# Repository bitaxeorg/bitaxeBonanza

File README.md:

bitaxeBonanza quad Intel BZM2 ASIC miner.

It is still an untested prototype! Don't build this expecting it to work out of the box. Do build it if you want to hack on some rad stuff.

- [Open Hardware License](LICENSE); Real Open Source.
	- [KiCAD](https://kicad.org) design files. 
- Four Intel BZM2 ASICs, powered in series.
	- Each BZM2 is [nominally](doc/specs.md) 0.7V with approx 350 GH/s @ 1.15 GHz hash frequency.
	- On chip digital temperature and voltage sensors
	- ntime rolling
- 11-13V XT30 input voltage
- TPS546D24S single-phase voltage regulator tuned for 2.8V output @ 20A
	- The voltage regulator backside power plane is exposed to hopefully thermally bond it with the main heatsink. 
- New fan control strategy (no more EMC2101)
- ESP32S3 for [esp-miner](https://github.com/bitaxeorg/esp-miner) support.
- 9-bit serial ASIC support via RP2040
    - Preliminary support with the [bitaxe-raw-pico](https://github.com/bitaxeorg/bitaxe-raw/tree/pico) firmware.
- Gerbers _not_ provided to discourage side hacks and AliEx slop. HMU if you need help generating gerbers with KiCad.

©️ [bitaxeorg](https://bitaxe.org)

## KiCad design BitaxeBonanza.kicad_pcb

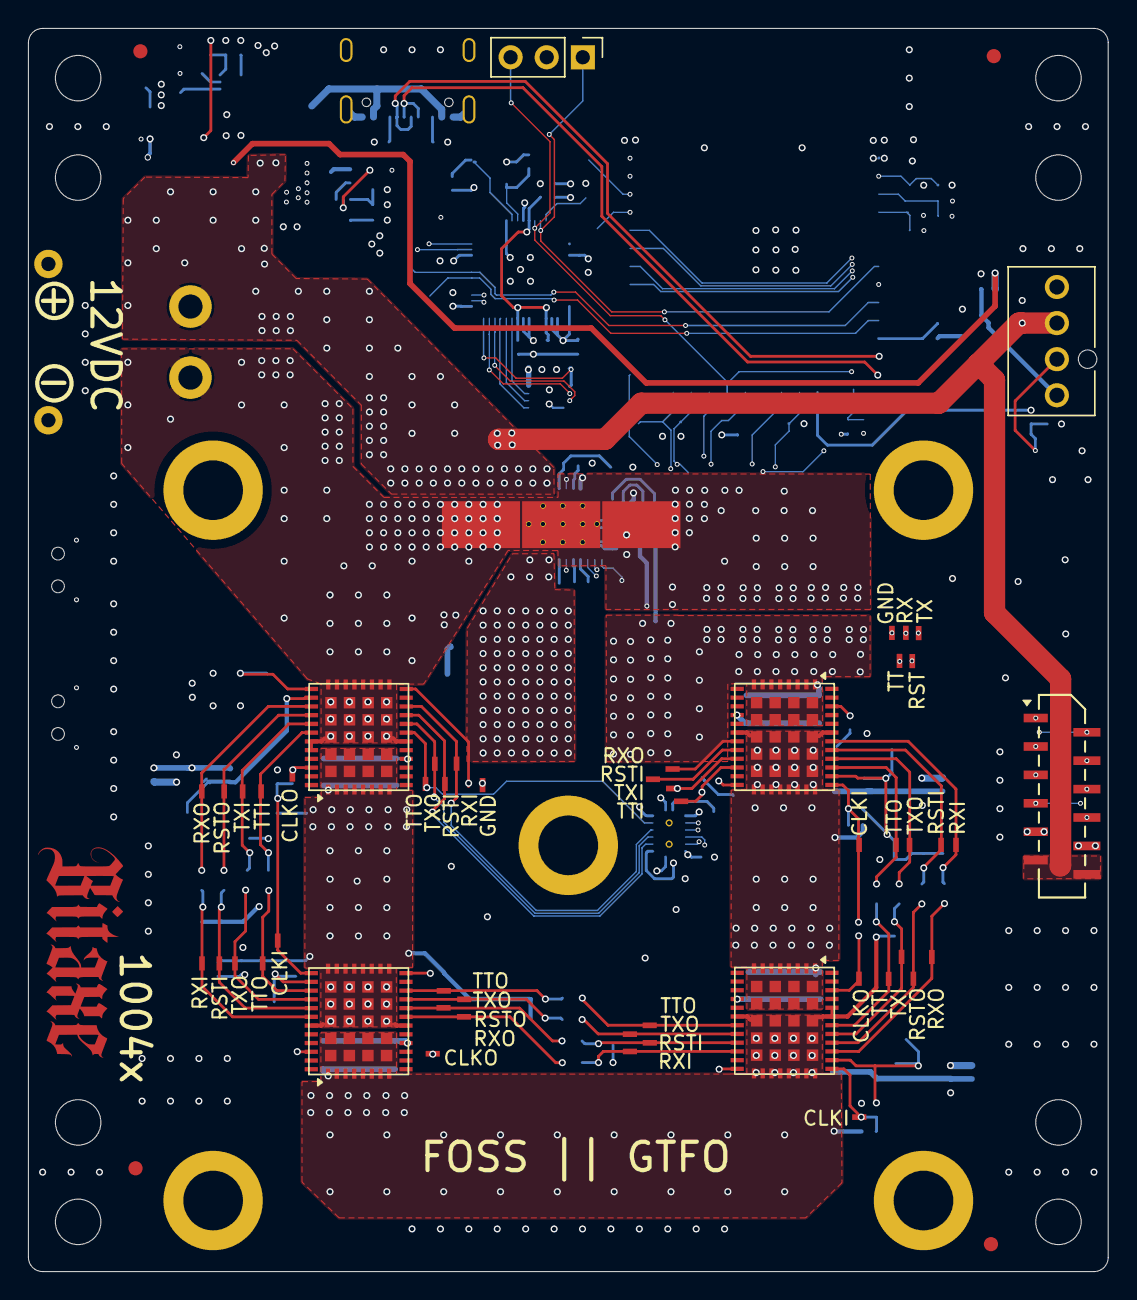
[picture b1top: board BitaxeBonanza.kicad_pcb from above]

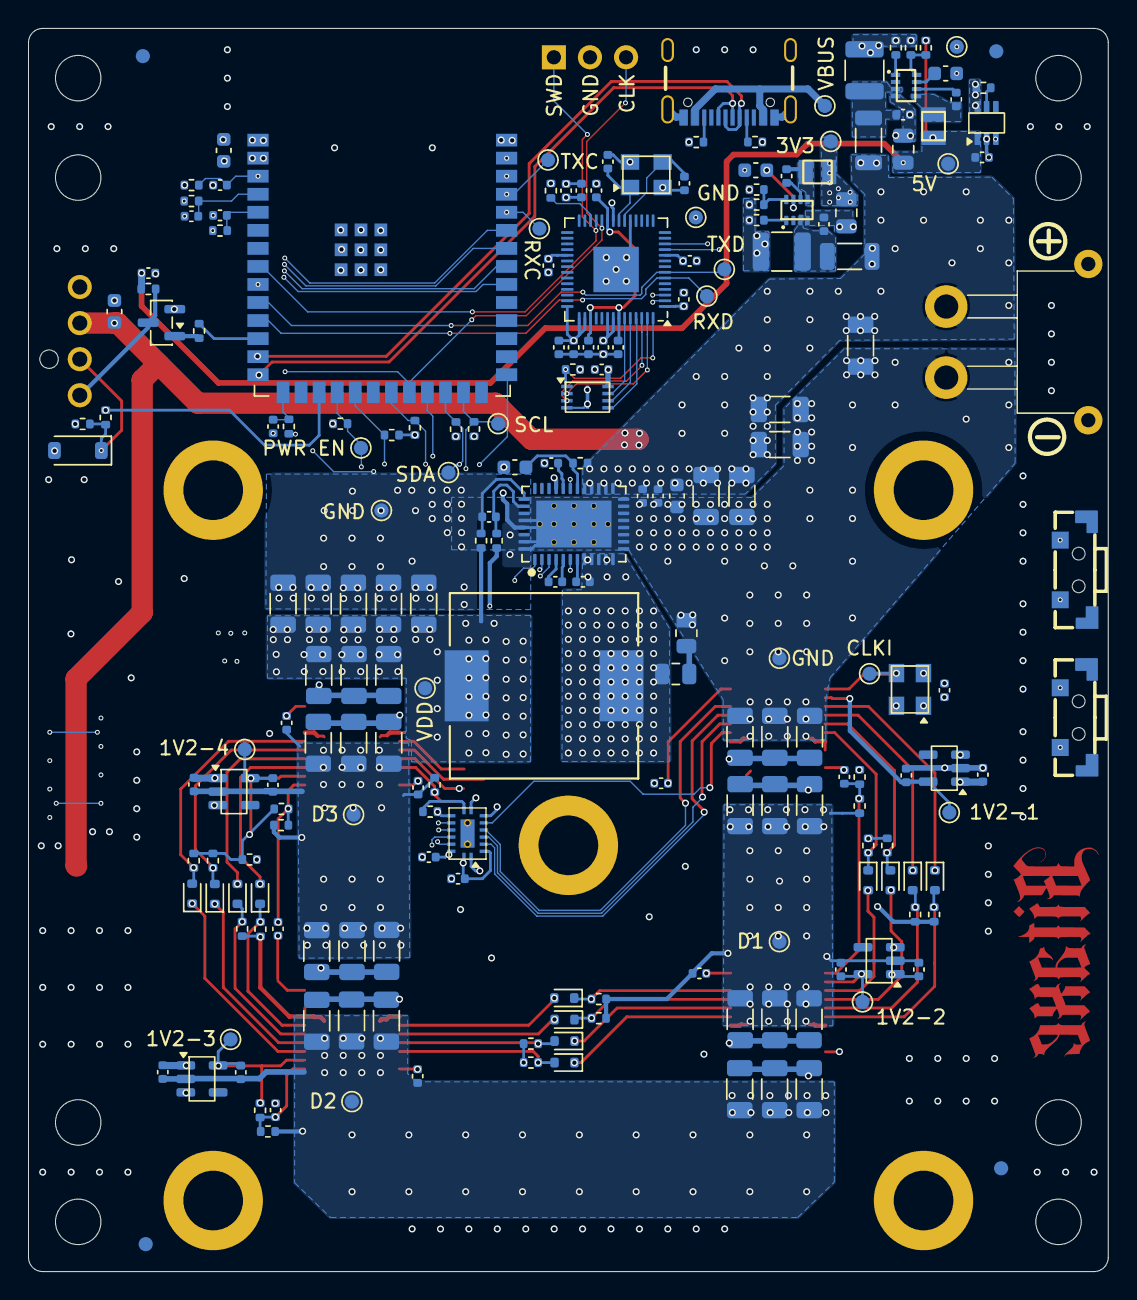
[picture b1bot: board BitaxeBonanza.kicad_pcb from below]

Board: 6 copper layers, 76.0 x 87.5 mm, 271 parts (210 on the bottom side), 135 nets.

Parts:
A1, A3: BZM2_MODE0; bzm2
A2, A4: BZM2_MODE1; bzm2
C2, C3, C4, C5, C6: 22uF; C_1206_3216Metric
C7, C15, C19, C25, C26, C27, C28, C34, C38, C39, C68, C72: 1uF; C_0402_1005Metric
C9, C10: 1uF; C_0603_1608Metric
C11: 4.7uF; C_0402_1005Metric
C13: 4.7nF; C_0402_1005Metric
C14: 2.2nF; C_0402_1005Metric
C16, C32, C36, C37, C40, C41, C42, C43, C44, C45, C46, C51, C52, C55, C56, C57, C58, C59, C67, C69, C70, C77: 0.1uF; C_0402_1005Metric
C17: 1000pF; C_0805_2012Metric
C18: 100pF; C_0402_1005Metric
C20: 47uF; C_1206_3216Metric
C21, C22, C23, C24, C83, C84, C85, C91, C92, C93, C99, C100, C101, C107, C108, C109, C115, C116, C117, C123, C124, C125, C131, C132, C133, C139, C140, C141: 100uF; C_1206_3216Metric
C33, C35: 30pF; C_0402_1005Metric
C47, C76: 10uF; C_0603_1608Metric
C48: 12pF; C_0402_1005Metric
C49, C50: 10uF; C_1210_3225Metric
C53, C54: 33nF; C_0603_1608Metric
C60, C61, C62, C63, C64: 120pF; C_0402_1005Metric
C65, C66: 22uF; C_0805_2012Metric
C142, C143, C144: 1000pF; C_0402_1005Metric
D1, D2, D3, D4, D5, D6, D7, D8, D9, D10, D11, D12: BAS516; D_SOD-523
D13: 3.3V Zener; D_SOD-123
FB1, FB2: FerriteBead; L_1206_3216Metric
FID1, FID2, FID3, FID4: Fiducial; Fiducial_1mm_Mask2mm
H1, H2, H3, H4, H5, H6, H7, H8: MountingHole_Pad; MountingHole_3.2mm_M3
HS1: Heatsink; Heatsink-5hole-BitaxeGT
J1: XT30; XT30PW-M
J2: Conn_01x03; PinHeader_1x03_P2.54mm_Vertical
J4: Conn_01x04; fan_connector
J5: Conn_01x12; CONN12_1-1735042-2
J6: TYPE-C-31-M-12; USB-C_SMD-TYPE-C-31-M-12_1
L1: 1.2uH; SRP1245A-180M_BRN
L2, L3: 1.5uH; IND-SMD_L2.0-W1.6
NT1: NetTie_2; NetTie-2_SMD_Pad0.2mmx1mm
Q1: BSS138; SOT-23
R1, R4, R17, R35, R36, R37, R38, R39, R40, R41, R42, R43, R44, R45, R46, R47, R48, R49, R50, R51, R52: 1k; R_0402_1005Metric
R2, R3, R9, R14, R22, R25, R34: 10k; R_0402_1005Metric
R5: 10; R_0402_1005Metric
R6: 1; R_0805_2012Metric
R7, R8: 49.9; R_0402_1005Metric
R15, R28: 15k; R_0402_1005Metric
R16: 49.9k; R_0402_1005Metric
R18, R19, R20, R21: 4.7k; R_0402_1005Metric
R23, R24, R30, R31, R32, R53: 5.1k; R_0402_1005Metric
R26: 20k; R_0402_1005Metric
R27: 47k; R_0402_1005Metric
R29: 27k; R_0402_1005Metric
R33: 5.6k; R_0402_1005Metric
SW3, SW4: SWITCH-SPST; SW-SMD_TC-S3601-3.5-260G-F0.6
TP1: PWR EN; TestPoint_Pad_D1.0mm
TP2: 1V2-2; TestPoint_Pad_D1.0mm
TP3: 1V2-3; TestPoint_Pad_D1.0mm
TP4: 1V2-4; TestPoint_Pad_D1.0mm
TP5: SDA; TestPoint_Pad_D1.0mm
TP6, TP13, TP32, TP51, TP55: RSTI; TestPoint_Pad_1.0x0.4mm
TP7: VDD; TestPoint_Pad_D1.0mm
TP8: SCL; TestPoint_Pad_D1.0mm
TP10: CLKI; TestPoint_Pad_D1.0mm
TP11, TP28, TP43: TTI; TestPoint_Pad_1.0x0.4mm
TP12, TP29, TP44: TXI; TestPoint_Pad_1.0x0.4mm
TP14, TP31, TP38, TP46: RXO; TestPoint_Pad_1.0x0.4mm
TP16: TXC; TestPoint_Pad_D1.0mm
TP17, TP33, TP40, TP50, TP54: TXO; TestPoint_Pad_1.0x0.4mm
TP18: 1V2-1; TestPoint_Pad_D1.0mm
TP19, TP26, TP27, TP61: GND; TestPoint_Pad_D1.0mm
TP20, TP36, TP52, TP56: RXI; TestPoint_Pad_1.0x0.4mm
TP21, TP34, TP41, TP49, TP53: TTO; TestPoint_Pad_1.0x0.4mm
TP22, TP69: GND; TestPoint_Pad_1.0x0.4mm
TP23: RXC; TestPoint_Pad_D1.0mm
TP24: TXD; TestPoint_Pad_D1.0mm
TP25: RXD; TestPoint_Pad_D1.0mm
TP30, TP39, TP45: RSTO; TestPoint_Pad_1.0x0.4mm
TP35, TP48, TP57: CLKI; TestPoint_Pad_1.0x0.4mm
TP37, TP42, TP47: CLKO; TestPoint_Pad_1.0x0.4mm
TP58: D1; TestPoint_Pad_D1.0mm
TP59: D2; TestPoint_Pad_D1.0mm
TP60: D3; TestPoint_Pad_D1.0mm
TP62: 3V3; TestPoint_Pad_D1.0mm
TP63: 5V; TestPoint_Pad_D1.0mm
TP64: VBUS; TestPoint_Pad_D1.0mm
TP65: TX; TestPoint_Pad_1.0x0.4mm
TP66: RX; TestPoint_Pad_1.0x0.4mm
TP67: TT; TestPoint_Pad_1.0x0.4mm
TP68: RST; TestPoint_Pad_1.0x0.4mm
U1, U3, U4, U6: MCP1824T-1202E/OT; SOT-23-5
U2: TPS546D24SRVFR; LQFN40-CLIP
U5: W25Q16JVUXIQ TR; USON-8_UX_2x3x0p6_WIN
U8: SN74AXC4T774; BQB0016A-MFG
U9: TPS22919DCKR; DCK0006A_N
U11: RP2040; RP2040-QFN-56-1EP_7x7mm_P0.4mm_EP3.2x3.2mm
U12: ESP32-S3-WROOM-1
U13, U14: TPS62933DRLR; SOT-583-8_L2.1-W1.2-P0.50-LS1.6-BR
U15, U16, U17: STHW4-DU-HN050206; PAD-SMD_L5.0-W2.0_STHW4-DU-HN050206
Y1: 12MHz; XTAL_ECS-120-20-33-CKM-TR3
Y2: 50MHz; OSC_ECS-3225MV-500-CN-TR

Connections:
/3V3: C32.2, C39.2, C40.2, C41.2, C42.2, C43.2, C44.2, C45.2, C46.2, C47.1, C59.1, C65.2, L2.2, R14.1, R16.2, R18.1, R19.2, R20.2, R21.2, R22.2, R27.2, R33.2, TP62.1 (1_1), U5.8 (VCC), U8.15 (VCCB), U11.1 (IOVDD), U11.10 (IOVDD), U11.22 (IOVDD), U11.33 (IOVDD), U11.42 (IOVDD), U11.43 (ADC_AVDD), U11.44 (VREG_IN), U11.48 (USB_VDD), U11.49 (IOVDD), U12.2 (3V3)
/5V: C34.1, C66.2, C77.1, L3.2, R29.2, R34.2, TP63.1 (1_1), U9.1 (IN)
/5V_SWITCH: C7.2, C25.2, C27.2, C68.2, R17.1, U1.1 (VIN), U1.3 (EN), U3.1 (VIN), U3.3 (EN), U4.1 (VIN), U4.3 (EN), U6.1 (VIN), U6.3 (EN), U9.6 (OUT)
/12V: C2.1, C3.1, C4.1, C5.1, C6.1, C9.1, C13.1, C14.1, C76.1, FB1.1, FB2.1, J1.1 (+V), J4.2, J5.11, J5.12, R5.1, U2.21 (PVIN), U2.22 (PVIN), U2.23 (PVIN), U2.24 (PVIN), U2.25 (PVIN)
/ASIC/1V2-1: A1.30 (VDDIO), C57.1, C58.1, C72.2, TP18.1 (1_1), U6.5 (VOUT), U8.2 (DIR2), U8.8 (DIR4), U8.16 (VCCA), Y2.1 (EN), Y2.4 (VIN)
/ASIC/1V2-2: A2.30 (VDDIO), C19.2, R37.2, R38.1, R39.1, TP2.1 (1_1), U1.5 (VOUT)
/ASIC/1V2-3: A3.30 (VDDIO), C26.2, R43.2, R44.1, R45.1, TP3.1 (1_1), U3.5 (VOUT)
/ASIC/1V2-4: A4.30 (VDDIO), C28.2, R4.1, R49.2, R50.1, R51.1, TP4.1 (1_1), U4.5 (VOUT)
/ASIC/GND2: A1.2 (VDD), A1.3 (VDD), A1.4 (VDD), A1.5 (VDD), A1.6 (VDD), A1.7 (VDD), A1.8 (VDD), A1.41 (VDD), A1.42 (VDD), A1.49 (VDD), A1.50 (VDD), A1.51 (VDD), A1.52 (VDD), A1.59 (VDD), A1.60 (VDD), A2.14 (VSS), A2.21 (VSS), A2.22 (VSS), A2.23 (VSS), A2.24 (VSS), A2.25 (VSS), A2.26 (VSS), A2.27 (VSS), A2.28 (VSS), A2.35 (VSS), A2.43 (VSS), A2.44 (VSS), A2.45 (VSS), A2.46 (VSS), A2.47 (VSS), A2.48 (VSS), A2.53 (VSS), A2.54 (VSS), A2.55 (VSS), A2.56 (VSS), A2.57 (VSS), A2.58 (VSS), C7.1, C19.1, C63.2, C83.2, C84.2, C85.2, C107.1, C108.1, C109.1, R40.2, R41.2, R42.2, R53.1, TP58.1 (1_1), U1.2 (GND)
/ASIC/GND3: A2.2 (VDD), A2.3 (VDD), A2.4 (VDD), A2.5 (VDD), A2.6 (VDD), A2.7 (VDD), A2.8 (VDD), A2.41 (VDD), A2.42 (VDD), A2.49 (VDD), A2.50 (VDD), A2.51 (VDD), A2.52 (VDD), A2.59 (VDD), A2.60 (VDD), A3.14 (VSS), A3.21 (VSS), A3.22 (VSS), A3.23 (VSS), A3.24 (VSS), A3.25 (VSS), A3.26 (VSS), A3.27 (VSS), A3.28 (VSS), A3.35 (VSS), A3.36 (PINSEL), A3.43 (VSS), A3.44 (VSS), A3.45 (VSS), A3.46 (VSS), A3.47 (VSS), A3.48 (VSS), A3.53 (VSS), A3.54 (VSS), A3.55 (VSS), A3.56 (VSS), A3.57 (VSS), A3.58 (VSS), C25.1, C26.1, C62.2, C99.2, C100.2, C101.2, C123.1, C124.1, C125.1, R32.1, R46.2, R47.2, R48.2, TP59.1 (1_1), U3.2 (GND)
/ASIC/GND4: A3.2 (VDD), A3.3 (VDD), A3.4 (VDD), A3.5 (VDD), A3.6 (VDD), A3.7 (VDD), A3.8 (VDD), A3.41 (VDD), A3.42 (VDD), A3.49 (VDD), A3.50 (VDD), A3.51 (VDD), A3.52 (VDD), A3.59 (VDD), A3.60 (VDD), A4.14 (VSS), A4.21 (VSS), A4.22 (VSS), A4.23 (VSS), A4.24 (VSS), A4.25 (VSS), A4.26 (VSS), A4.27 (VSS), A4.28 (VSS), A4.35 (VSS), A4.43 (VSS), A4.44 (VSS), A4.45 (VSS), A4.46 (VSS), A4.47 (VSS), A4.48 (VSS), A4.53 (VSS), A4.54 (VSS), A4.55 (VSS), A4.56 (VSS), A4.57 (VSS), A4.58 (VSS), C27.1, C28.1, C60.2, C61.2, C115.2, C116.2, C117.2, C139.1, C140.1, C141.1, R9.2, R31.1, R52.2, TP60.1 (1_1), U4.2 (GND)
/ASIC/REFCLKIN1: A1.29 (REFCLKIN), TP10.1 (1_1), Y2.3 (OUT)
/ASIC/REFCLKIN2: A2.29 (REFCLKIN), C142.2, R39.2, R40.1, TP35.1 (1_1)
/ASIC/REFCLKIN3: A3.29 (REFCLKIN), C143.2, R45.2, R46.1, TP57.1 (1_1)
/ASIC/REFCLKIN4: A4.29 (REFCLKIN), C144.2, R51.2, R52.1, TP48.1 (1_1)
/ASIC/REFCLKOUT1: A1.38 (REFCLKOUT1), C142.1, TP37.1 (1_1)
/ASIC/REFCLKOUT2: A2.38 (REFCLKOUT1), C143.1, TP42.1 (1_1)
/ASIC/REFCLKOUT3: A3.38 (REFCLKOUT1), C144.1, TP47.1 (1_1)
/ASIC/RST_1V2: A1.17 (RESET_IN), TP6.1 (1_1), U8.3 (A1)
/ASIC/RST_3V3: TP68.1 (1_1), U8.14 (B1), U12.39 (GPIO1/TOUCH1/ADC1_CH0)
/ASIC/RX_1V2: A1.18 (RX_IN), TP20.1 (1_1), U8.5 (A3)
/ASIC/RX_3V3: TP66.1 (1_1), U8.12 (B3), U11.11 (GPIO8)
/ASIC/TRIP_1V2: A1.15 (TRIP_OUT), TP21.1 (1_1), U8.6 (A4)
/ASIC/TRIP_3V3: TP67.1 (1_1), U8.11 (B4), U12.38 (GPIO2/TOUCH2/ADC1_CH1)
/ASIC/TX_1V2: A1.16 (TX_OUT), TP17.1 (1_1), U8.4 (A2)
/ASIC/TX_3V3: TP65.1 (1_1), U8.13 (B2), U11.12 (GPIO9)
/ASIC/bypass1-1/out: A1.1 (VDD_INT_1), C83.1, C84.1, C85.1
/ASIC/bypass1-2/in: A1.12 (VDD_INT_2), C91.2, C92.2, C93.2
/ASIC/bypass2-1/out: A2.1 (VDD_INT_1), C99.1, C100.1, C101.1
/ASIC/bypass2-2/in: A2.12 (VDD_INT_2), C107.2, C108.2, C109.2
/ASIC/bypass3-1/out: A3.1 (VDD_INT_1), C115.1, C116.1, C117.1
/ASIC/bypass3-2/in: A3.12 (VDD_INT_2), C123.2, C124.2, C125.2
/ASIC/bypass4-1/out: A4.1 (VDD_INT_1), C131.1, C132.1, C133.1
/ASIC/bypass4-2/in: A4.12 (VDD_INT_2), C139.2, C140.2, C141.2
/ASIC/shifter1-2/RESET_IN: A2.33 (RESET_IN), D3.A, R37.1, TP32.1 (1_1)
/ASIC/shifter1-2/RESET_OUT: A1.32 (RESET_OUT), D3.K, TP30.1 (1_1)
/ASIC/shifter1-2/RX_IN: A2.34 (RX_IN), D4.A, R38.2, TP36.1 (1_1)
/ASIC/shifter1-2/RX_OUT: A1.31 (RX_OUT), D4.K, TP31.1 (1_1)
/ASIC/shifter1-2/TRIP_IN: A1.34 (TRIP_IN), D1.K, R35.1, TP28.1 (1_1)
/ASIC/shifter1-2/TRIP_OUT: A2.31 (TRIP_OUT), D1.A, TP34.1 (1_1)
/ASIC/shifter1-2/TX_IN: A1.33 (TX_IN), D2.K, R36.1, TP29.1 (1_1)
/ASIC/shifter1-2/TX_OUT: A2.32 (TX_OUT), D2.A, TP33.1 (1_1)
/ASIC/shifter2-3/RESET_IN: A3.17 (RESET_IN), D7.A, R43.1, TP55.1 (1_1)
/ASIC/shifter2-3/RESET_OUT: A2.16 (RESET_OUT), D7.K, TP39.1 (1_1)
/ASIC/shifter2-3/RX_IN: A3.18 (RX_IN), D8.A, R44.2, TP56.1 (1_1)
/ASIC/shifter2-3/RX_OUT: A2.15 (RX_OUT), D8.K, TP38.1 (1_1)
/ASIC/shifter2-3/TRIP_IN: A2.18 (TRIP_IN), D5.K, R41.1, TP41.1 (1_1)
/ASIC/shifter2-3/TRIP_OUT: A3.15 (TRIP_OUT), D5.A, TP53.1 (1_1)
/ASIC/shifter2-3/TX_IN: A2.17 (TX_IN), D6.K, R42.1, TP40.1 (1_1)
/ASIC/shifter2-3/TX_OUT: A3.16 (TX_OUT), D6.A, TP54.1 (1_1)
/ASIC/shifter3-4/RESET_IN: A4.33 (RESET_IN), D11.A, R49.1, TP51.1 (1_1)
/ASIC/shifter3-4/RESET_OUT: A3.32 (RESET_OUT), D11.K, TP45.1 (1_1)
/ASIC/shifter3-4/RX_IN: A4.34 (RX_IN), D12.A, R50.2, TP52.1 (1_1)
/ASIC/shifter3-4/RX_OUT: A3.31 (RX_OUT), D12.K, TP46.1 (1_1)
/ASIC/shifter3-4/TRIP_IN: A3.34 (TRIP_IN), D9.K, R47.1, TP43.1 (1_1)
/ASIC/shifter3-4/TRIP_OUT: A4.31 (TRIP_OUT), D9.A, TP49.1 (1_1)
/ASIC/shifter3-4/TX_IN: A3.33 (TX_IN), D10.K, R48.1, TP44.1 (1_1)
/ASIC/shifter3-4/TX_OUT: A4.32 (TX_OUT), D10.A, TP50.1 (1_1)
/Data/1V1: C36.2, C37.2, C38.2, U11.23 (DVDD), U11.45 (VREG_VOUT), U11.50 (DVDD)
/Data/5V_EN: U9.3 (ON), U12.23 (GPIO21)
/Data/DISP_GPIO1: J5.8, U12.35 (MTMS/GPIO42)
/Data/DISP_GPIO2: J5.7, U12.34 (MTDI/GPIO41/CLK_OUT1)
/Data/DISP_RX: J5.4, U12.33 (MTDO/GPIO40/CLK_OUT2)
/Data/DISP_TX: J5.5, U12.32 (MTCK/GPIO39/CLK_OUT3/SUBSPICS1)
/Data/EN: C48.1, R22.1, SW3.2, U12.3 (EN)
/Data/ESP32_RX_CTRL: TP23.1 (1_1), U11.2 (GPIO0), U12.36 (U0RXD/GPIO44/CLK_OUT2)
/Data/ESP32_RX_DATA: TP25.1 (1_1), U11.6 (GPIO4), U12.11 (GPIO18/U1RXD/ADC2_CH7/CLK_OUT3)
/Data/ESP32_TX_CTRL: TP16.1 (1_1), U11.3 (GPIO1), U12.37 (U0TXD/GPIO43/CLK_OUT1)
/Data/ESP32_TX_DATA: TP24.1 (1_1), U11.7 (GPIO5), U12.10 (GPIO17/U1TXD/ADC2_CH6)
/Data/FAN_PWM: R1.2, U12.12 (GPIO8/TOUCH8/ADC1_CH7/SUBSPICS1)
/Data/FAN_TACH: R2.2, U12.17 (GPIO9/TOUCH9/ADC1_CH8/FSPIHD/SUBSPIHD)
/Data/IO0: SW4.2, U12.27 (GPIO0/BOOT*)
/Data/PWR_EN: R3.2, TP1.1 (1_1), U2.27 (EN/UVLO), U12.18 (GPIO10/TOUCH10/ADC1_CH9/FSPICS0/FSPIIO4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)
/Data/QSPI_SCLK: U5.6 (CLK), U11.52 (QSPI_SCLK)
/Data/QSPI_SD0: U5.5 (DI(IO0)), U11.53 (QSPI_SD0)
/Data/QSPI_SD1: U5.2 (DO(IO1)), U11.55 (QSPI_SD1)
/Data/QSPI_SD2: U5.3 (/WP(IO2)), U11.54 (QSPI_SD2)
/Data/QSPI_SD3: U5.7 (/HOLDOR/RESET(IO3)), U11.51 (QSPI_SD3)
/Data/QSPI_SS: R14.2, U5.1 (/CS), U11.56 (QSPI_SS)
/Data/SCL: R19.1, TP8.1 (1_1), U2.3 (PMB_CLK), U12.25 (GPIO48/SPICLK_N/SUBSPICLK_N_DIFF)
/Data/SDA: R18.2, TP5.1 (1_1), U2.2 (PMB_DATA), U12.24 (GPIO47/SPICLK_P/SUBSPICLK_P_DIFF)
/Data/SMB_ALRT: R20.1, U2.6 (SMB_ALRT), U12.21 (GPIO13/TOUCH13/ADC2_CH2/FSPIQ/FSPIIO7/S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)
/Data/SWCLK: J2.3, J5.1, U11.24 (SWCLK), U12.22 (GPIO14/TOUCH14/ADC2_CH3/FSPIWP/FSPIDQS/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)
/Data/SWD-BRIDGE: J2.1, U11.25 (SWD), U12.8 (GPIO15/U0RTS/ADC2_CH4/XTAL_32K_P)
/Data/SWD-DISP: J5.2, U12.9 (GPIO16/U0CTS/ADC2_CH5/XTAL_32K_NH5)
/Data/USB_D+: J6.A6 (DP1), J6.B6 (DP2), U12.14 (GPIO20/U1CTS/ADC2_CH9/CLK_OUT1/USB_D+)
/Data/USB_D-: J6.A7 (DN1), J6.B7 (DN2), U12.13 (GPIO19/U1RTS/ADC2_CH8/CLK_OUT2/USB_D-)
/Data/XIN: C35.2, U11.20 (XIN), Y1.3
/Data/XOUT: C33.2, U11.21 (XOUT), Y1.1
/Power/AGND: C10.1, NT1.2, U2.29 (MSEL2), U2.37 (AGND)
/Power/BP1v5: C15.1, U2.4 (BP1V5)
/Power/PGOOD: R21.1, U2.1 (PGD), U12.19 (GPIO11/TOUCH11/ADC2_CH0/FSPID/FSPIIO5/S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)
/Power/SW1: C16.2, C17.1, L1.1, U2.8 (SW), U2.9 (SW), U2.10 (SW), U2.11 (SW), U2.12 (SW)
/Power/V5reg_1: C11.2, U2.28 (VDD5)
/VDD: A4.2 (VDD), A4.3 (VDD), A4.4 (VDD), A4.5 (VDD), A4.6 (VDD), A4.7 (VDD), A4.8 (VDD), A4.41 (VDD), A4.42 (VDD), A4.49 (VDD), A4.50 (VDD), A4.51 (VDD), A4.52 (VDD), A4.59 (VDD), A4.60 (VDD), C20.2, C21.2, C22.2, C23.2, C24.2, C131.2, C132.2, C133.2, L1.2, R7.1, TP7.1 (1_1)
/fan/FAN_PWM_PIN: J4.4, Q1.3 (D), R34.1
/fan/FAN_TACH_PIN: D13.1 (K), J4.3, R2.1, R33.1
GND: A1.14 (VSS), A1.21 (VSS), A1.22 (VSS), A1.23 (VSS), A1.24 (VSS), A1.25 (VSS), A1.26 (VSS), A1.27 (VSS), A1.28 (VSS), A1.35 (VSS), A1.36 (PINSEL), A1.43 (VSS), A1.44 (VSS), A1.45 (VSS), A1.46 (VSS), A1.47 (VSS), A1.48 (VSS), A1.53 (VSS), A1.54 (VSS), A1.55 (VSS), A1.56 (VSS), A1.57 (VSS), A1.58 (VSS), C2.2, C3.2, C4.2, C5.2, C6.2, C9.2, C11.1, C13.2, C14.2, C20.1, C21.1, C22.1, C23.1, C24.1, C32.1, C33.1, C34.2, C35.1, C36.1, C37.1, C38.1, C39.1, C40.1, C41.1, C42.1, C43.1, C44.1, C45.1, C46.1, C47.2, C48.2, C49.1, C50.1, C51.2, C52.2, C53.1, C54.1, C57.2, C58.2, C59.2, C64.2, C65.1, C66.1, C67.2, C68.1, C69.2, C70.2, C72.1, C76.2, C77.2, C91.1, C92.1, C93.1, D13.2 (A), J1.2 (GND), J2.2, J4.1, J5.3, J5.6, J5.9, J5.10, J6.1 (SHIELD), J6.2 (EH), J6.3 (EH), J6.4 (EH), J6.A1B12 (GND), J6.B1A12 (GND), NT1.1, Q1.2 (S), R3.1, R6.2, R8.2, R15.1, R23.1, R24.1, R25.1, R26.1, R28.1, R30.1, R35.2, R36.2, SW3.1, SW4.1, TP19.1 (1_1), TP22.1 (1_1), TP26.1 (1_1), TP27.1 (1_1), TP61.1 (1_1), TP69.1 (1_1), U2.13 (PGND), U2.14 (PGND), U2.15 (PGND), U2.16 (PGND), U2.17 (PGND), U2.18 (PGND), U2.19 (PGND), U2.20 (PGND), U2.36 (NC), U2.39 (BCX_CLK), U2.40 (BCX_DAT), U2.41 (PAD), U5.4 (GND), U5.9 (EPAD), U6.2 (GND), U8.1 (DIR1), U8.7 (DIR3), U8.10 (GND), U9.2 (GND), U11.19 (TESTEN), U11.57 (GND), U12.1 (GND), U12.40 (GND), U12.41 (GND), U13.4 (GND), U14.4 (GND), U15.1 (1_1), U16.1 (1_1), U17.1 (1_1), Y1.2, Y1.4, Y2.2 (GND)
unnamed: A1.20 (REFCLKOUT2), C64.1
unnamed: A2.20 (REFCLKOUT2), C63.1
unnamed: A3.20 (REFCLKOUT2), C62.1
unnamed: A4.38 (REFCLKOUT1), C60.1
unnamed: A4.20 (REFCLKOUT2), C61.1
unnamed: A4.16 (RESET_OUT), TP13.1 (1_1)
unnamed: A4.15 (RX_OUT), TP14.1 (1_1)
unnamed: A4.18 (TRIP_IN), R9.1, TP11.1 (1_1)
unnamed: A4.17 (TX_IN), R4.2, TP12.1 (1_1)
unnamed: C17.2, R6.1
unnamed: J6.A5 (CC1), R23.2
unnamed: J6.B5 (CC2), R24.2
unnamed: J6.A4B9 (VBUS), J6.B4A9 (VBUS), TP64.1 (1_1)
unnamed: Q1.1 (G), R1.1
unnamed: C10.2, R5.2, U2.26 (AVIN)
unnamed: C16.1, U2.7 (BOOT)
unnamed: C15.2, U2.5 (DRTN)
unnamed: C18.2, R8.1, U2.34 (GOSNS)
unnamed: C18.1, R7.2, U2.33 (VOSNS)
unnamed: R26.2, U8.9 (OE)
unnamed: R17.2, U9.5 (QOD)
unnamed: R16.1, U11.26 (RUN)
unnamed: C67.1, R31.2, U12.15 (GPIO3/TOUCH3/ADC1_CH2*)
unnamed: C69.1, R32.2, U12.4 (GPIO4/TOUCH4/ADC1_CH3)
unnamed: C70.1, R53.2, U12.5 (GPIO5/TOUCH5/ADC1_CH4)
unnamed: C55.1, U13.6 (BST)
unnamed: R27.1, R28.2, U13.8 (FB)
unnamed: R15.2, U13.1 (RT)
unnamed: C53.2, U13.7 (SS)
unnamed: C55.2, L2.1, U13.5 (SW)
unnamed: C49.2, C51.1, FB1.2, U13.3 (VIN)
unnamed: C56.1, U14.6 (BST)
unnamed: R29.1, R30.2, U14.8 (FB)
unnamed: R25.2, U14.1 (RT)
unnamed: C54.2, U14.7 (SS)
unnamed: C56.2, L3.1, U14.5 (SW)
unnamed: C50.2, C52.1, FB2.2, U14.3 (VIN)

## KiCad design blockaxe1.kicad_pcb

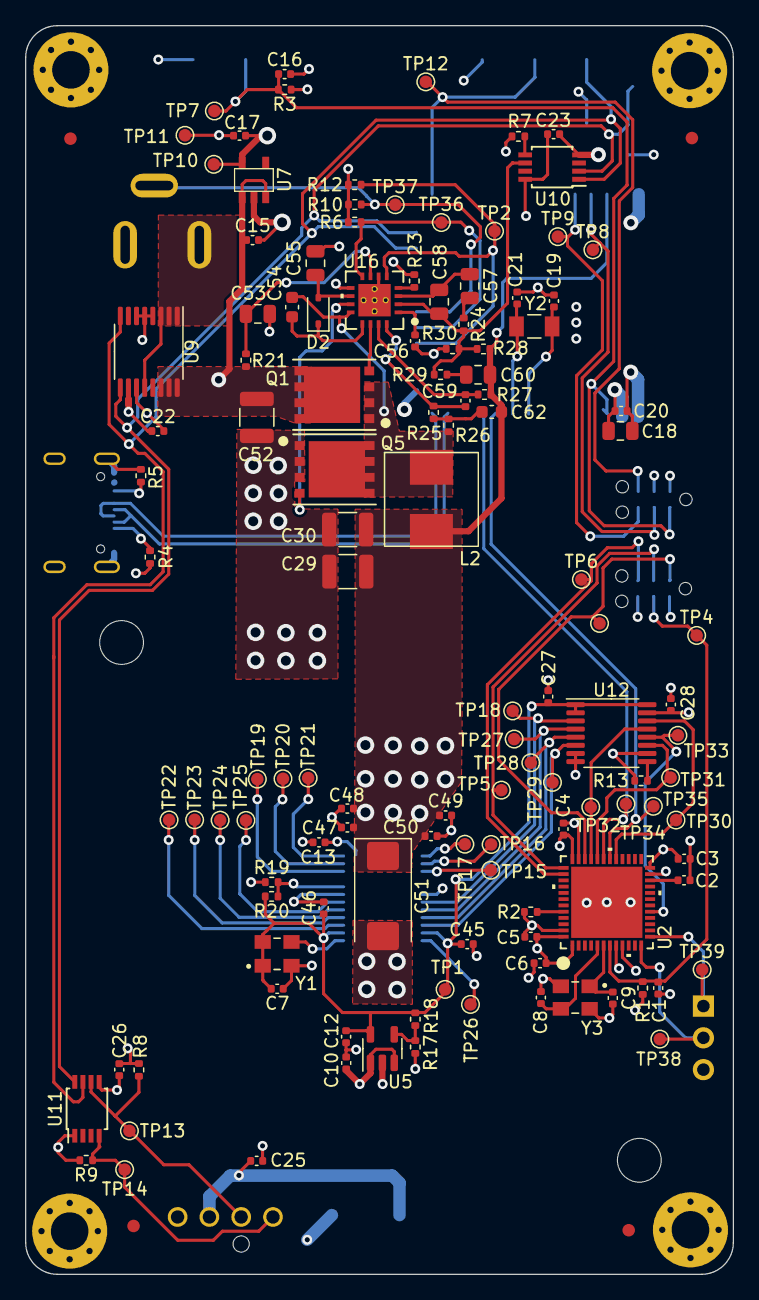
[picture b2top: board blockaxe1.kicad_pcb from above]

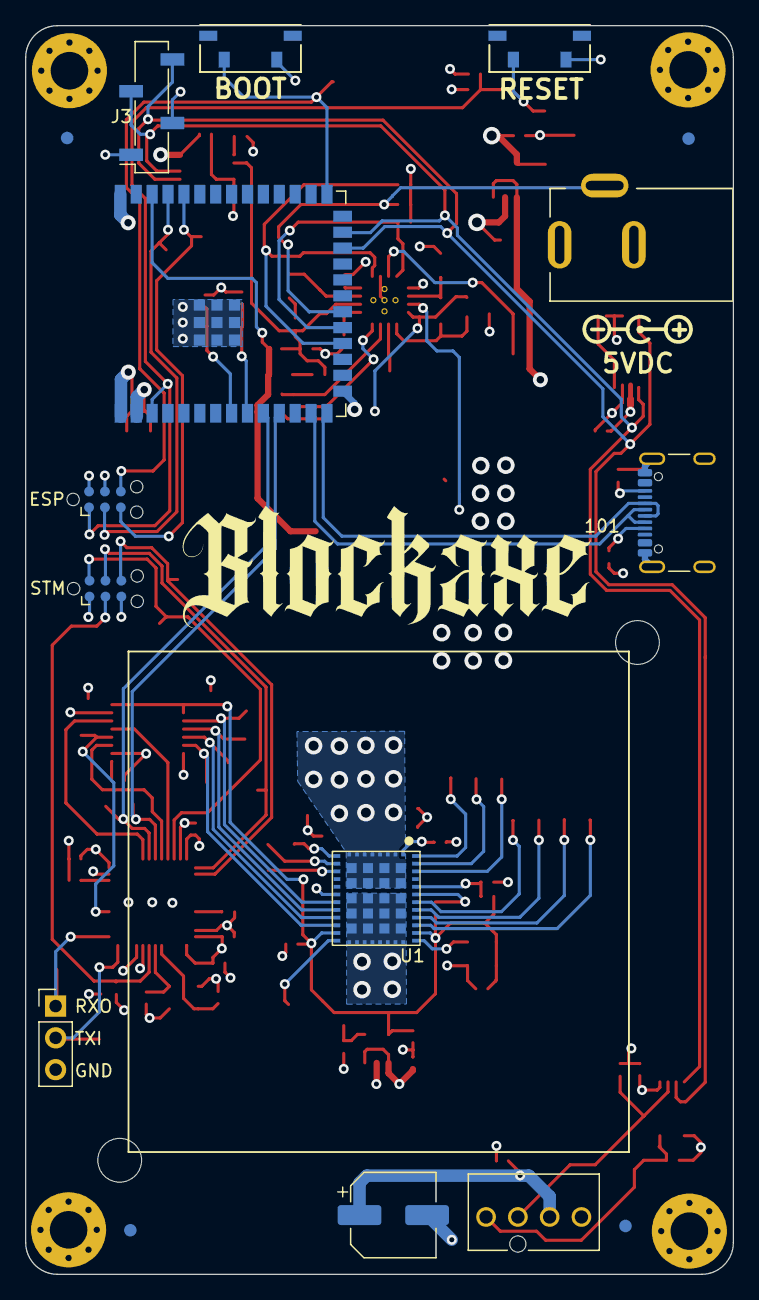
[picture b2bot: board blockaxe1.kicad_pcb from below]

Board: 4 copper layers, 56.5 x 99.8 mm, 150 parts (17 on the bottom side), 75 nets.

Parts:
C1, C3, C4, C5, C6, C7, C10, C13, C20, C25, C26, C27, C28, C47, C48: 0.1uF; C_0402_1005Metric
C2: 4.7uF; C_0402_1005Metric
C8, C9: 20pF; C_0402_1005Metric
C12, C15, C16, C17, C22, C23, C45, C46, C49, C50: 1uF; C_0402_1005Metric
C18: 10uF; C_0805_2012Metric
C19, C21: 6.8pF; C_0402_1005Metric
C24: 220uF; CP_Elec_6.3x7.7
C29, C30, C52: 100uF; C_1210_3225Metric
C51: 330uF; CP_EIA-7343-31_Kemet-D_Pad2.25x2.55mm_HandSolder
C53, C55: 1uF; C_0805_2012Metric
C54, C62: 0.22uF; C_0603_1608Metric
C56: 0.027uF; C_0402_1005Metric
C57: 0.001uF; C_0805_2012Metric
C58: 82pF; C_0805_2012Metric
C59: 100pF; C_0402_1005Metric
C60: 220pF; C_0805_2012Metric
D2: XBS104S13R-G; D_SOD-323
FID1, FID2, FID3, FID4, FID5, FID6, FID7, FID8: Fiducial; Fiducial_1mm_Mask2mm
H1, H2, H3, H4: MountingHole_Pad; MountingHole_3mm_Pad_Via
H5, H6: MountingHole; MountingHole_3.5mm
J1, J2: TC2030-IDC; Tag-Connect_TC2030-IDC-NL_2x03_P1.27mm_Vertical
J3: Conn_01x04; PinSocket_1x04_P2.54mm_Vertical_SMD_Pin1Right
J4: USB_C_Receptacle_USB2.0; USB_C_Receptacle_GCT_USB4105-xx-A_16P_TopMnt_Horizontal
J5: EJ503A; MPD_EJ503A
J6: Conn_01x04; 470531000
J7: Conn_01x03; PinHeader_1x03_P2.54mm_Vertical
L2: 100nH; FP0805R1-R10-R
Q1, Q5: CSD17312Q5; DQH8
R1, R2, R3, R6, R9, R12: 10k; R_0402_1005Metric
R4, R5: 5.1k; R_0402_1005Metric
R7: 80.6k; R_0402_1005Metric
R8: 5.6k; R_0402_1005Metric
R10: 1M; R_0402_1005Metric
R13, R28: 20k; R_0402_1005Metric
R17: 130k 1%; R_0402_1005Metric
R18: 182k 1%; R_0402_1005Metric
R19, R20: 0; R_0402_1005Metric
R21: 2.21; R_0402_1005Metric
R23: 11.8k; R_0402_1005Metric
R24: 5.23k; R_0402_1005Metric
R25, R27: 665; R_0402_1005Metric
R26: 2.67k; R_0402_1005Metric
R29: 442; R_0402_1005Metric
R30: 120k; R_0402_1005Metric
SW1, SW2: TL3330AF260QG; SW_TL3330_EWI
TP1, TP2, TP3, TP4, TP5, TP6, TP7, TP8, TP9, TP10, TP11, TP12, TP13, TP14, TP15, TP16, TP17, TP18, TP19, TP20, TP21, TP22, TP23, TP24, TP25, TP26, TP27, TP28, TP29, TP30, TP31, TP32, TP33, TP34, TP35, TP36, TP37, TP38, TP39: TestPoint; TestPoint_Pad_D1.0mm
U1: bzm2
U2: STM32F410CBU6; UFQFPN-48_7X7X0P55MM
U3: polarity
U5: ADP171AUJ-R7; TSOT-23-5
U7: RT9080-33GJ5
U8: ESP32-S3-WROOM-1
U9: INA260; TSSOP-16_4.4x5mm_P0.65mm
U10: DS4432U+; TSSOP-8_3x3mm_P0.65mm
U11: EMC2101; TSSOP-8_3x3mm_P0.65mm
U12: SN74AVC4T774; TSSOP-16_4.4x5mm_P0.65mm
U16: LM27402; SQB16A
Y1: 50MHz; OSC_ECS-3225MV-500-CN-TR
Y2: 32.768kHz; SC32S-7PF20PPM
Y3: 8MHz; XTAL_ECS-240-8-33-AGN-TR

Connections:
/5V: C15.1, C24.1, C25.1, C52.1, J6.2, Q1.5 (D), R21.1, U7.1 (VIN), U7.3 (EN), U9.14 (IN-), U9.15 (IN-), U9.16 (IN-)
/ASIC/1V2: C7.2, C12.1, C27.1, C45.1, C46.1, R18.1, R20.2, TP1.1, U1.19 (VDDIO), U1.30 (VDDIO), U5.5 (VOUT), U12.1 (DIR1), U12.2 (DIR2), U12.16 (VCCA), Y1.1 (EN), Y1.4 (VIN)
/ASIC/CLK: U1.29 (REFCLKIN), Y1.3 (OUT)
/ASIC/RESET_IN: TP28.1, U1.17 (RESET_IN), U12.5 (A3)
/ASIC/RX_IN: TP29.1, U1.18 (RX_IN), U12.6 (A4)
/ASIC/TRIP_OUT: TP18.1, U1.15 (TRIP_OUT), U12.3 (A1)
/ASIC/TX_OUT: TP27.1, U1.16 (TX_OUT), U12.4 (A2)
/COREV: C29.1, C30.1, C47.1, C48.1, C49.1, C50.1, C51.1, C60.1, C62.2, L2.2, R27.1, R28.1, U1.2 (VDD), U1.3 (VDD), U1.4 (VDD), U1.5 (VDD), U1.6 (VDD), U1.7 (VDD), U1.8 (VDD), U1.41 (VDD), U1.42 (VDD), U1.49 (VDD), U1.50 (VDD), U1.51 (VDD), U1.52 (VDD), U1.59 (VDD), U1.60 (VDD), U8.38 (GPIO2/TOUCH2/ADC1_CH1)
/ESP32/EN: C16.1, J2.1, R3.2, SW1.2, TP7.1, U8.3 (EN)
/ESP32/IO0: J2.6, SW2.2, TP12.1, U8.27 (GPIO0/BOOT*)
/ESP32/P_RX: J2.5, TP9.1, U8.36 (U0RXD/GPIO44/CLK_OUT2)
/ESP32/P_TX: J2.3, TP8.1, U8.37 (U0TXD/GPIO43/CLK_OUT1)
/ESP32/RX: TP34.1, U2.31 (PA10), U8.11 (GPIO18/U1RXD/ADC2_CH7/CLK_OUT3)
/ESP32/TX: TP35.1, U2.30 (PA9), U8.10 (GPIO17/U1TXD/ADC2_CH6)
/ESP32/XIN32: C19.1, U8.8 (GPIO15/U0RTS/ADC2_CH4/XTAL_32K_P), Y2.1
/ESP32/XOUT32: C21.1, U8.9 (GPIO16/U0CTS/ADC2_CH5/XTAL_32K_NH5), Y2.2
/Fan/FAN_PWM: J6.4, R9.1, TP14.1, U11.4 (FAN)
/Fan/FAN_TACH: J6.3, R8.1, TP13.1, U11.6 (ALERT/TACH)
/PGOOD: R6.2, TP36.1, U8.19 (GPIO11/TOUCH11/ADC2_CH0/FSPID/FSPIIO5/S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), U16.8 (PGOOD)
/PLUG_SENSE: J5.3, R10.2, TP37.1, U8.20 (GPIO12/TOUCH12/ADC2_CH1/FSPICLK/FSPIIO6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)
/PWR_EN: R12.2, TP2.1, U8.18 (GPIO10/TOUCH10/ADC1_CH9/FSPICS0/FSPIIO4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), U16.5 (EN)
/Power/OUT0: C58.2, R24.2, R28.2, R29.2, R30.1, U10.6 (OUT0), U16.2 (FB)
/Power/SW: C54.2, L2.1, Q1.1, Q1.2, Q1.3 (S), Q5.5 (D), R26.1, U16.12 (SW)
/SCL: J3.3, U8.25 (GPIO48/SPICLK_N/SUBSPICLK_N_DIFF), U9.9 (SCL), U10.2 (SCL), U11.8 (SMCLK)
/SDA: J3.4, U8.24 (GPIO47/SPICLK_P/SUBSPICLK_P_DIFF), U9.8 (SDA), U10.1 (SDA), U11.7 (SMDATA)
/STM32/RESET: TP33.1, U2.17 (PA7), U12.12 (B3)
/STM32/RX2: J7.1, TP39.1, U2.13 (PA3)
/STM32/RX6: TP32.1, U2.33 (PA12), U12.13 (B2)
/STM32/SWCLK: J1.4, TP5.1, U2.37 (PA14)
/STM32/SWDIO: J1.2, TP3.1, U2.34 (PA13)
/STM32/SWO: J1.6, TP6.1, U2.38 (PA15)
/STM32/SWRESET: C1.1, J1.3, R1.1, TP4.1, U2.7 (NRST)
/STM32/TRIP: TP30.1, U2.29 (PA8), U12.14 (B1)
/STM32/TX2: J7.2, TP38.1, U2.12 (PA2)
/STM32/TX6: TP31.1, U2.32 (PA11), U12.11 (B4)
GND: C1.2, C2.2, C3.2, C4.2, C5.2, C6.2, C7.1, C8.2, C9.1, C10.2, C12.2, C13.2, C15.2, C16.2, C17.2, C18.2, C19.2, C20.2, C21.2, C22.2, C23.2, C24.2, C25.2, C26.2, C27.2, C28.2, C29.2, C30.2, C45.2, C46.2, C47.2, C48.2, C49.2, C50.2, C51.2, C52.2, C53.2, C55.2, C56.2, H1.1, H2.1, H3.1, H4.1, J1.5, J2.4, J3.1, J4.A1B12 (GND), J4.B1A12 (GND), J4.S1 (SHIELD), J5.2, J6.1, J7.3, Q5.1, Q5.2, Q5.3 (S), R2.1, R4.1, R5.1, R7.2, R13.1, R17.1, R19.1, R23.2, R30.2, SW1.1, SW2.1, TP11.1, U1.14 (VSS), U1.21 (VSS), U1.22 (VSS), U1.23 (VSS), U1.24 (VSS), U1.25 (VSS), U1.26 (VSS), U1.27 (VSS), U1.28 (VSS), U1.35 (VSS), U1.43 (VSS), U1.44 (VSS), U1.45 (VSS), U1.46 (VSS), U1.47 (VSS), U1.48 (VSS), U1.53 (VSS), U1.54 (VSS), U1.55 (VSS), U1.56 (VSS), U1.57 (VSS), U1.58 (VSS), U2.8 (VSSA/VREF-), U2.23 (VSS), U2.35 (VSS), U2.47 (PDR_ON), U2.49 (EXP), U5.2 (GND), U7.2 (GND), U8.1 (GND), U8.40 (GND), U8.41 (GND), U9.4 (A1), U9.5 (A0), U9.6 (GND), U9.11 (GND), U10.4 (GND), U11.5 (GND), U12.7 (DIR3), U12.8 (DIR4), U12.10 (GND), U16.6 (SYNC), U16.9 (GND), U16.17 (PAD), Y1.2 (GND), Y3.2, Y3.4
IN+: J5.1, U9.1 (IN+), U9.2 (IN+), U9.3 (IN+), U9.12 (VBUS)
unnamed: C57.2, R24.1
unnamed: C60.2, R29.1
unnamed: C62.1, R25.1, R26.2
unnamed: C55.1, D2.2 (A), U16.10 (VDD)
unnamed: C54.1, D2.1 (K), U16.13 (CBOOT)
unnamed: J4.A5 (CC1), R4.2
unnamed: J4.B5 (CC2), R5.2
unnamed: Q1.4 (G), U16.14 (HG)
unnamed: Q5.4 (G), U16.11 (LG)
unnamed: R19.2, R20.1, U1.36 (PINSEL)
unnamed: TP19.1, U1.38 (REFCLKOUT1)
unnamed: TP26.1, U1.20 (REFCLKOUT2)
unnamed: TP23.1, U1.32 (RESET_OUT)
unnamed: TP22.1, U1.31 (RX_OUT)
unnamed: TP15.1, U1.11 (TCK)
unnamed: TP16.1, U1.10 (TDI)
unnamed: TP17.1, U1.9 (TDO)
unnamed: TP20.1, U1.39 (TMS)
unnamed: TP25.1, U1.34 (TRIP_IN)
unnamed: TP21.1, U1.40 (TRST)
unnamed: TP24.1, U1.33 (TX_IN)
unnamed: C13.1, U1.1 (VDD_INT_1)
unnamed: R2.2, U2.44 (BOOT)
unnamed: C8.1, U2.5 (OSC_IN), Y3.3
unnamed: C9.2, U2.6 (OSC_OUT), Y3.1
unnamed: C2.1, U2.22 (VCAP_1)
unnamed: R17.2, R18.2, U5.4 (ADJ)
unnamed: J4.A7 (D-), J4.B7 (D-), U8.13 (GPIO19/U1RTS/ADC2_CH8/CLK_OUT2/USB_D-)
unnamed: J4.A6 (D+), J4.B6 (D+), U8.14 (GPIO20/U1CTS/ADC2_CH9/CLK_OUT1/USB_D+)
unnamed: R7.1, U10.5 (FS0)
unnamed: R13.2, U12.9 (OE)
unnamed: C57.1, C58.1, U16.3 (COMP)
unnamed: C59.2, R25.2, U16.16 (CS+)
unnamed: C59.1, R27.2, U16.15 (CS-)
unnamed: R23.1, U16.4 (FADJ)
unnamed: C56.1, U16.1 (SS/TRACK)
unnamed: C53.1, R21.2, U16.7 (VIN)
VDD: C3.1, C4.1, C5.1, C6.1, C10.1, C17.1, C18.1, C20.1, C22.1, C23.1, C26.1, C28.1, J1.1, J2.2, J3.2, R1.2, R3.1, R6.1, R8.2, R9.2, R10.1, R12.1, TP10.1, U2.1 (VBAT), U2.9 (VDDA/VREF+), U2.24 (VDD), U2.36 (VDD), U2.48 (VDD), U5.1 (VIN), U5.3 (EN), U7.5 (VOUT), U8.2 (3V3), U8.15 (GPIO3/TOUCH3/ADC1_CH2*), U9.10 (VS), U10.8 (VCC), U11.1 (VDD), U12.15 (VCCB)

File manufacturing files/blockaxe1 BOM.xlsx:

Qty | Ref Des | Value | DK | PARTNO | DNP
15 | C1, C3, C4, C5, C6, C7, C10, C13, C20, C25, C26, C27, C28, C47, C48 | 0.1uF | 1292-1639-1-ND | 0402X104K100CT
1 | C2 | 4.7uF | 1276-1482-1-ND | CL05A475MP5NRNC
2 | C8, C9 | 20pF | 490-GCM1555C1H200JA16DCT-ND | GCM1555C1H200JA16D
10 | C12, C15, C16, C17, C22, C23, C45, C46, C49, C50 | 1uF | 587-5514-1-ND | EMK105BJ105MV-F
1 | C18 | 10uF | 399-C0805C106K8PAC7800CT-ND | C0805C106K8PAC7800
2 | C19, C21 | 6.8pF | 399-C0402C689C5GAC7867CT-ND | C0402C689C5GAC7867
1 | C24 | 220uF | 732-8422-1-ND | 865080345012
3 | C29, C30, C52 | 100uF | 490-9969-1-ND | GRM32ER61A107ME20L
1 | C51 | 330uF | 718-1028-1-ND | 293D337X9010E2TE3
2 | C53, C55 | 1uF | 1276-1066-1-ND | CL21B105KAFNNNE
2 | C54, C62 | 0.22uF | 490-3290-1-ND | GRM188R71E224KA88D
1 | C56 | 0.027uF | 1292-1200-1-ND | 0402B273K250CT
1 | C57 | 0.001uF | 478-KGM21NR71H102KTCT-ND | KGM21NR71H102KT
1 | C58 | 82pF | 311-1110-1-ND | CC0805JRNPO9BN820
1 | C59 | 100pF | 311-1024-1-ND | CC0402JRNPO9BN101
1 | C60 | 220pF | 1276-1164-1-ND | CL21C221JBANNNC
1 | D2 | XBS104S13R-G | 893-1188-1-ND | XBS104S13R-G
1 | J4 | USB_C_Receptacle_USB2.0 | 2073-USB4105-GF-ACT-ND | USB4105-GF-A
1 | J5 | EJ503A | EJ503A-ND | EJ503A
1 | J6 | Conn_01x04 | WM4330-ND | 0470531000
1 | L2 | 100nH | 283-FP0805R1-R10-RCT-ND | FP0805R1-R10-R
2 | Q1, Q5 | CSD17312Q5 | 296-27613-1-ND | CSD17312Q5
6 | R1, R2, R3, R6, R9, R12 | 10k | 311-10KJRCT-ND | RC0402JR-0710KL
2 | R4, R5 | 5.1k | RMCF0402JT5K10CT-ND | RMCF0402JT5K10
1 | R7 | 80.6k | 311-80.6KLRCT-ND | RC0402FR-0780K6L
1 | R8 | 5.6k | 13-RC0402FR-135K6LCT-ND | RC0402FR-135K6L
1 | R10 | 1M | 311-1.00MLRCT-ND | RC0402FR-071ML
2 | R13, R28 | 20k | 311-20.0KLRCT-ND | RC0402FR-0720KL
1 | R17 | 130k 1% | YAG2969CT-ND | RC0402FR-07130KL
1 | R18 | 182k 1% | YAG3015CT-ND | RC0402FR-07182KL
1 | R19 | 0 | RMCF0402ZT0R00CT-ND | RMCF0402ZT0R00
1 | R20 | 0 | RMCF0402ZT0R00CT-ND | RMCF0402ZT0R00 | DNP
1 | R21 | 2.21 | RMCF0402FT2R21CT-ND | RMCF0402FT2R21
1 | R23 | 11.8k | YAG2958CT-ND | RC0402FR-0711K8L
1 | R24 | 5.23k | YAG3195CT-ND | RC0402FR-075K23L
2 | R25, R27 | 665 | YAG3208CT-ND | RC0402FR-07665RL
1 | R26 | 2.67k | 311-2.67KLRCT-ND | RC0402FR-072K67L
1 | R29 | 442 | YAG3162CT-ND | RC0402FR-07442RL
1 | R30 | 120k | 311-120KLRCT-ND | RC0402FR-07120KL
2 | SW1, SW2 | TL3330AF260QG | EG4389CT-ND | TL3330AF260QG
1 | U1 | ~
1 | U2 | STM32F410CBU6 | 497-16240-ND | STM32F410CBU6
1 | U5 | ADP171AUJ-R7 | 505-ADP171AUJZ-R7CT-ND | ADP171AUJZ-R7
1 | U7 | RT9080-33GJ5 | 1028-1509-1-ND | RT9080-33GJ5
1 | U8 | ESP32-S3-WROOM-1 | 1965-ESP32-S3-WROOM-1-N16R8CT-ND | ESP32-S3-WROOM-1-N16R8
1 | U9 | INA260 | 296-45218-5-ND | INA260AIPW
1 | U10 | DS4432U+ | DS4432U+-ND | DS4432U+
1 | U11 | EMC2101 | EMC2101-R-ACZL-CT-ND | EMC2101-R-ACZL-TR
1 | U12 | SN74AVC4T774 | 296-24739-1-ND | SN74AVC4T774PWR
1 | U16 | LM27402 | LM27402SQ/NOPBCT-ND | LM27402SQ/NOPB
1 | Y1 | 50MHz |  | SX3M50.000E20F30THN
1 | Y2 | 32.768kHz | 728-1074-1-ND | SC32S-7PF20PPM
1 | Y3 | 8MHz | 50-ECS-80-12-33-JGN-CT-ND | ECS-80-12-33-JGN-TR

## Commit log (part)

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2023-11-16 initial import
2023-11-20 adding logo and docs
2023-12-01 added BZM2 footprint
2023-12-02 migrated over lots of bitaxe parts to blockaxe
2023-12-10 switched to the LM27402 buck regulator
2023-12-10 all the footprints are in?
2023-12-11 routed the buck reg. started placing board
2023-12-13 more placing and routing
2023-12-16 more routing. switched to RA buttons, moved the buck closer to the barrel
2023-12-20 finished routing. switched back to THT barrel
2023-12-21 added gerbers and BOM
2024-02-21 Switching to 1.2V Oscillator for #3 Switch the level shifter for #4
2024-02-21 added test points for #7
2024-02-21 changed buttons for #5 flipped display for #2
2024-02-22 switched barrel plug for #8. touched up schematic, DRC, generated BOM, generated Gerbers
2024-02-22 added stm32 crystal for #9
2024-02-22 generated gerbers, updated BOM C18 error
2024-03-15 update to KiCad8, DNP 32kHz crystal
2025-03-25 switch to bitaxeAura/GT base
2025-03-25 pulled in the BZM2 symbol and footprint
2025-05-22 added 8 ASICs in schematic
2025-06-11 moved ASIC bypass caps out to separate sheet
2025-06-12 added level shifters to schematic
2025-06-13 made the board double wide. rough ASIC and vreg placement.
2025-06-13 switch to EMC2302 for 2 fans and no temp sensor
2025-06-17 ASICs placed. most other parts placed.
2025-06-20 routing is done. Power planes look good. DRC pass
2025-06-24 moved fan connectors (and controller) up to the northern PCB edge
2025-08-05 updated TPS546D24 strapping values. fixed inductor value and output capacitors. PCB needs updating to add missing strapping footprint.
2025-09-13 changes esp32.kicad_sch case
2025-10-17 added BZM2 step model
2025-10-31 Update README with design issue notes
    Added notes about design issues that affect functionality.
2026-02-11 switch to the bitaxeBIRDS based pre-bonanza
2026-02-11 readme update
2026-02-11 updated schematic worksheet
2026-02-11 update pcbnew drawing sheet
2026-02-12 most placement and routing done
2026-02-12 add missing 3d, update render, update readme
2026-02-12 changed TPS82130 voltage regulators to TPSM82903. Connected ESP32<->RP2040 CTRL serial port. made top mounting holes plated.
2026-02-13 Filled out the BOM and added missing DK part numbers. thanks Claude
2026-02-13 add experimental AI BOM workflow
2026-02-15 switched to SMD FFC for the display connector
2026-02-15 switched back to TPS82130. added BOM partnumbers
2026-02-15 fix TPS82130 symbols
2026-02-15 fix pinsel connection on ASIC 3
2026-02-15 add missing courtyards and re-enable DRC check
2026-03-03 part silkscreen cleanup
2026-03-30 add missing cad files. bump to kicad v10
2026-04-07 minor silkscreen fixes. changed C1, C8 to 0805
